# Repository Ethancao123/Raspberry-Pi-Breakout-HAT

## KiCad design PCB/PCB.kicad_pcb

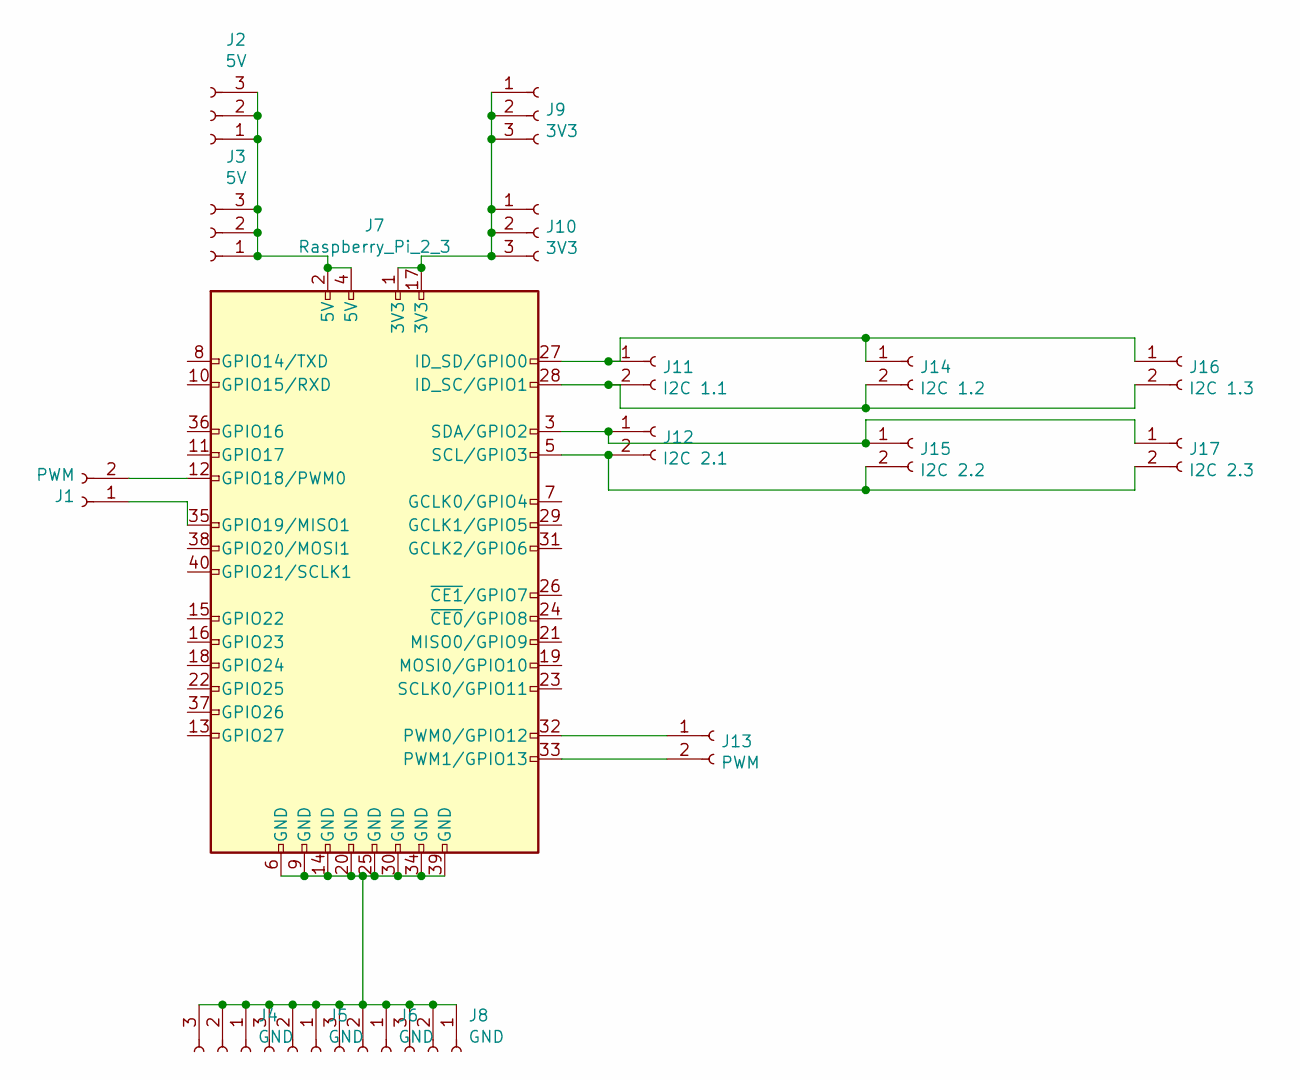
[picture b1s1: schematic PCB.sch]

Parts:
J1, J13: PWM; WJ250B-2pin
J2, J3: 5V; WJ250B-3pin
J4, J5, J6, J8: GND; WJ250B-3pin
J7: Raspberry_Pi_2_3; PinHeader_2x20_P2.54mm_Vertical
J9, J10: 3V3; WJ250B-3pin
J11: I2C 1.1; WJ250B-2pin
J12: I2C 2.1; WJ250B-2pin
J14: I2C 1.2; WJ250B-2pin
J15: I2C 2.2; WJ250B-2pin
J16: I2C 1.3; WJ250B-2pin
J17: I2C 2.3; WJ250B-2pin

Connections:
unnamed: J1.1, J7.35 (GPIO19/MISO1)
unnamed: J1.2, J7.12 (GPIO18/PWM0)
unnamed: J2.1, J2.2, J2.3, J3.1, J3.2, J3.3, J7.2 (5V), J7.4 (5V)
unnamed: J4.1, J4.2, J4.3, J5.1, J5.2, J5.3, J6.1, J6.2, J6.3, J7.6 (GND), J7.9 (GND), J7.14 (GND), J7.20 (GND), J7.25 (GND), J7.30 (GND), J7.34 (GND), J7.39 (GND), J8.1, J8.2, J8.3
unnamed: J7.1 (3V3), J7.17 (3V3), J9.1, J9.2, J9.3, J10.1, J10.2, J10.3
unnamed: J7.27 (ID_SD/GPIO0), J11.1, J14.1, J16.1
unnamed: J7.28 (ID_SC/GPIO1), J11.2, J14.2, J16.2
unnamed: J7.3 (SDA/GPIO2), J12.1, J15.1, J17.1
unnamed: J7.5 (SCL/GPIO3), J12.2, J15.2, J17.2
unnamed: J7.32 (PWM0/GPIO12), J13.1
unnamed: J7.33 (PWM1/GPIO13), J13.2

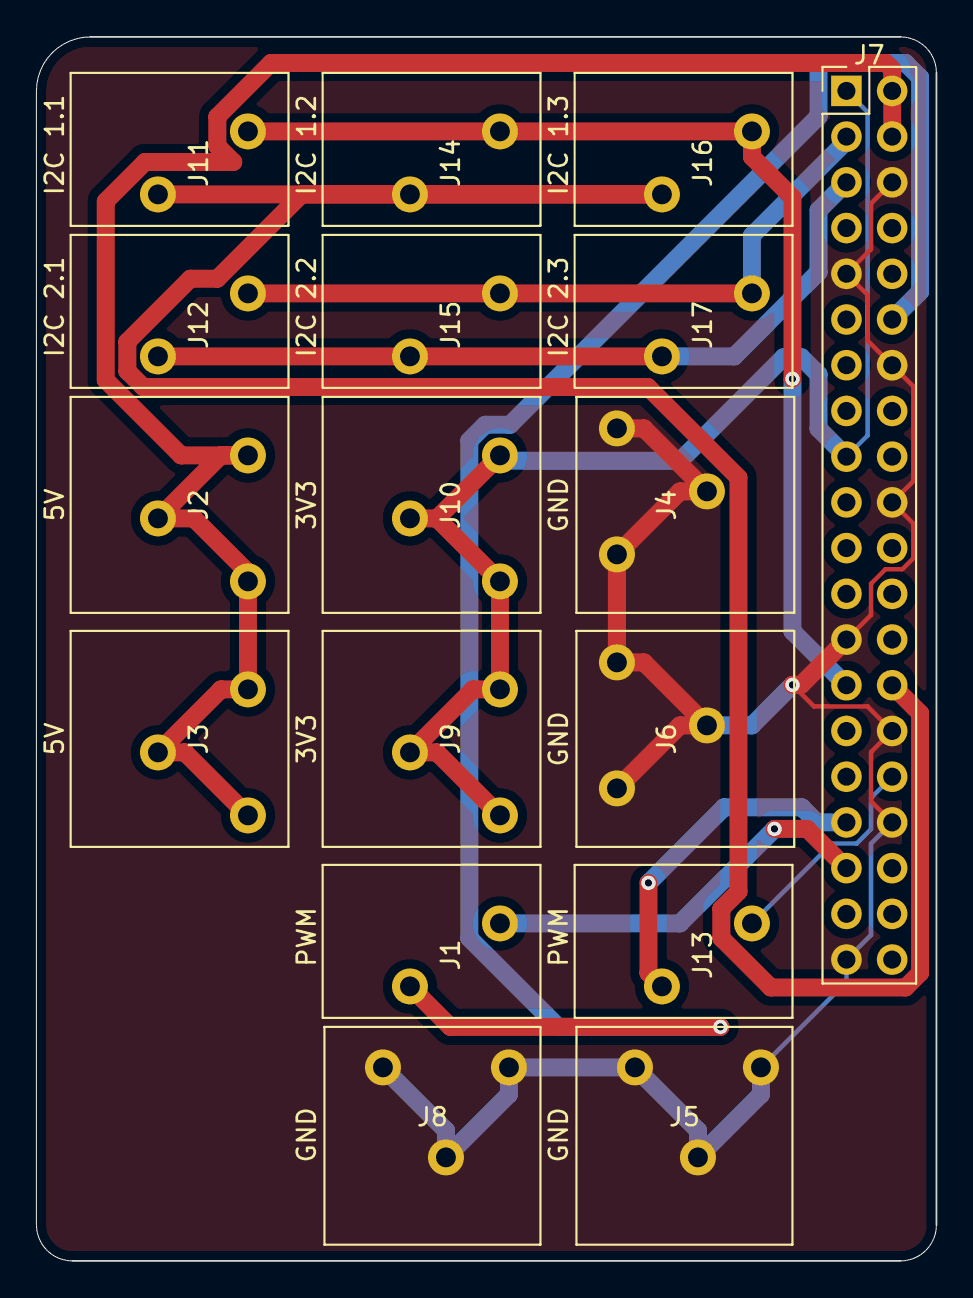
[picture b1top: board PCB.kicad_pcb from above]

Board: 2 copper layers, 50.0 x 68.0 mm, 17 parts (0 on the bottom side), 11 nets.

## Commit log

2022-01-17 Create Schematic
2022-01-20 Add gerber files
